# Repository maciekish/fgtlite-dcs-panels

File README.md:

# Another Warthog Project

This project has moved to https://github.com/maciekish/warthogathome

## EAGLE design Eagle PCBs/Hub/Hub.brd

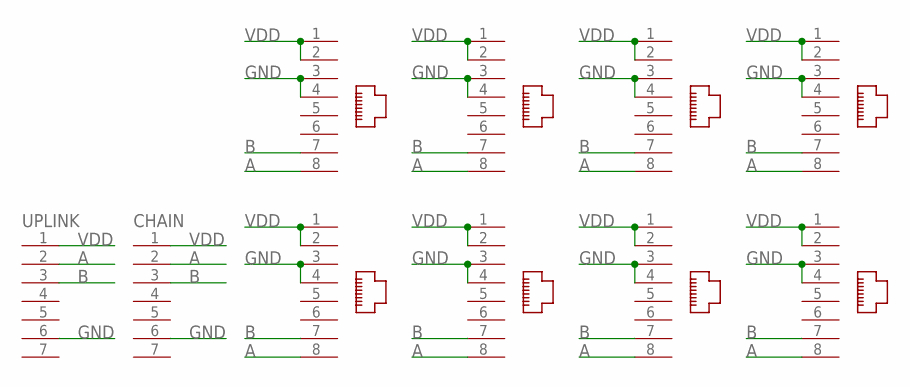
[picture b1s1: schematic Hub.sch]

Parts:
1, 2, 3, 4, 5, 6, 7, 8: RJ45-8P8C
CHAIN: GX12-7P
UPLINK: GX12-7P

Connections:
A: 1.8, 2.8, 3.8, 4.8, 5.8, 6.8, 7.8, 8.8, CHAIN.2, UPLINK.2
B: 1.7, 2.7, 3.7, 4.7, 5.7, 6.7, 7.7, 8.7, CHAIN.3, UPLINK.3
GND: 1.3, 1.4, 2.3, 2.4, 3.3, 3.4, 4.3, 4.4, 5.3, 5.4, 6.3, 6.4, 7.3, 7.4, 8.3, 8.4, CHAIN.6, UPLINK.6
VDD: 1.1, 1.2, 2.1, 2.2, 3.1, 3.2, 4.1, 4.2, 5.1, 5.2, 6.1, 6.2, 7.1, 7.2, 8.1, 8.2, CHAIN.1, UPLINK.1

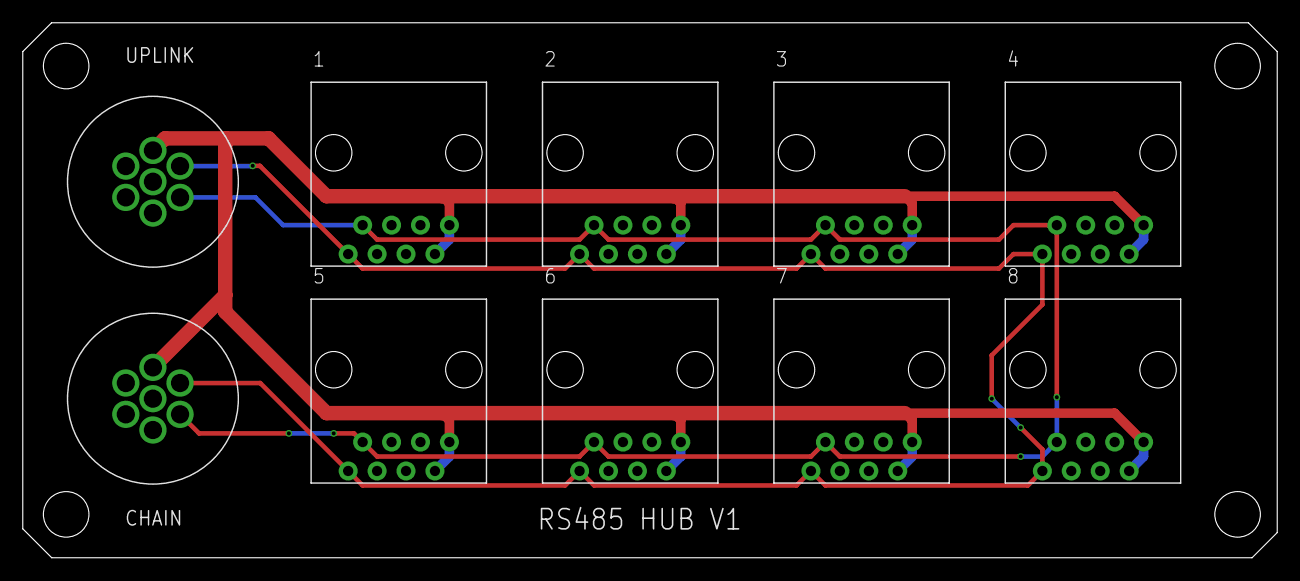
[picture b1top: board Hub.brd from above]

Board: 2 copper layers, 110.2 x 47.0 mm, 10 parts (0 on the bottom side), 4 nets.

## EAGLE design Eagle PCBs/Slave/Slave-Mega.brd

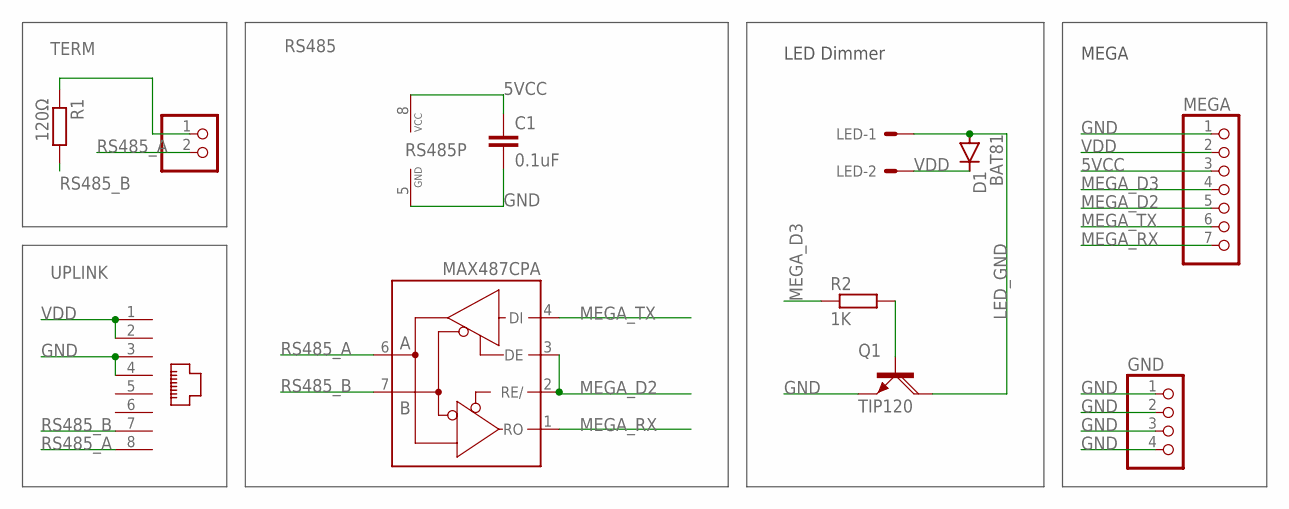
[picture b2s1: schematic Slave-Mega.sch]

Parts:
C1: 0.1uF; C025-025X050
D1: BAT81; DO34-7
GND: PINHD-1X4; 1X04
LED: KK-156-2
MEGA: PINHD-1X7; 1X07
Q1: TIP120; TO220AH
R1: 120Ω; 0204/7
R2: 1K; 0204/7
RS485: MAX487CPA; DIL08
TERM: PINHD-1X2; 1X02
UPLINK: RJ45-8P8C

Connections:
5VCC: C1.1, MEGA.3, RS485.8 (VCC)
GND: C1.2, GND.1, GND.2, GND.3, GND.4, MEGA.1, Q1.E, RS485.5 (GND), UPLINK.3, UPLINK.4
LED_GND: D1.A, LED.1, Q1.C
LED_PWM: Q1.B, R2.2
MEGA_D2: MEGA.5, RS485.2 (RE/), RS485.3 (DE)
MEGA_D3: MEGA.4, R2.1
MEGA_RX: MEGA.7, RS485.1 (RO)
MEGA_TX: MEGA.6, RS485.4 (DI)
RS485_A: RS485.6 (A), TERM.2, UPLINK.8
RS485_B: R1.2, RS485.7 (B), UPLINK.7
TERM: R1.1, TERM.1
VDD: D1.C, LED.2, MEGA.2, UPLINK.1, UPLINK.2

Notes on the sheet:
LED Dimmer
MEGA

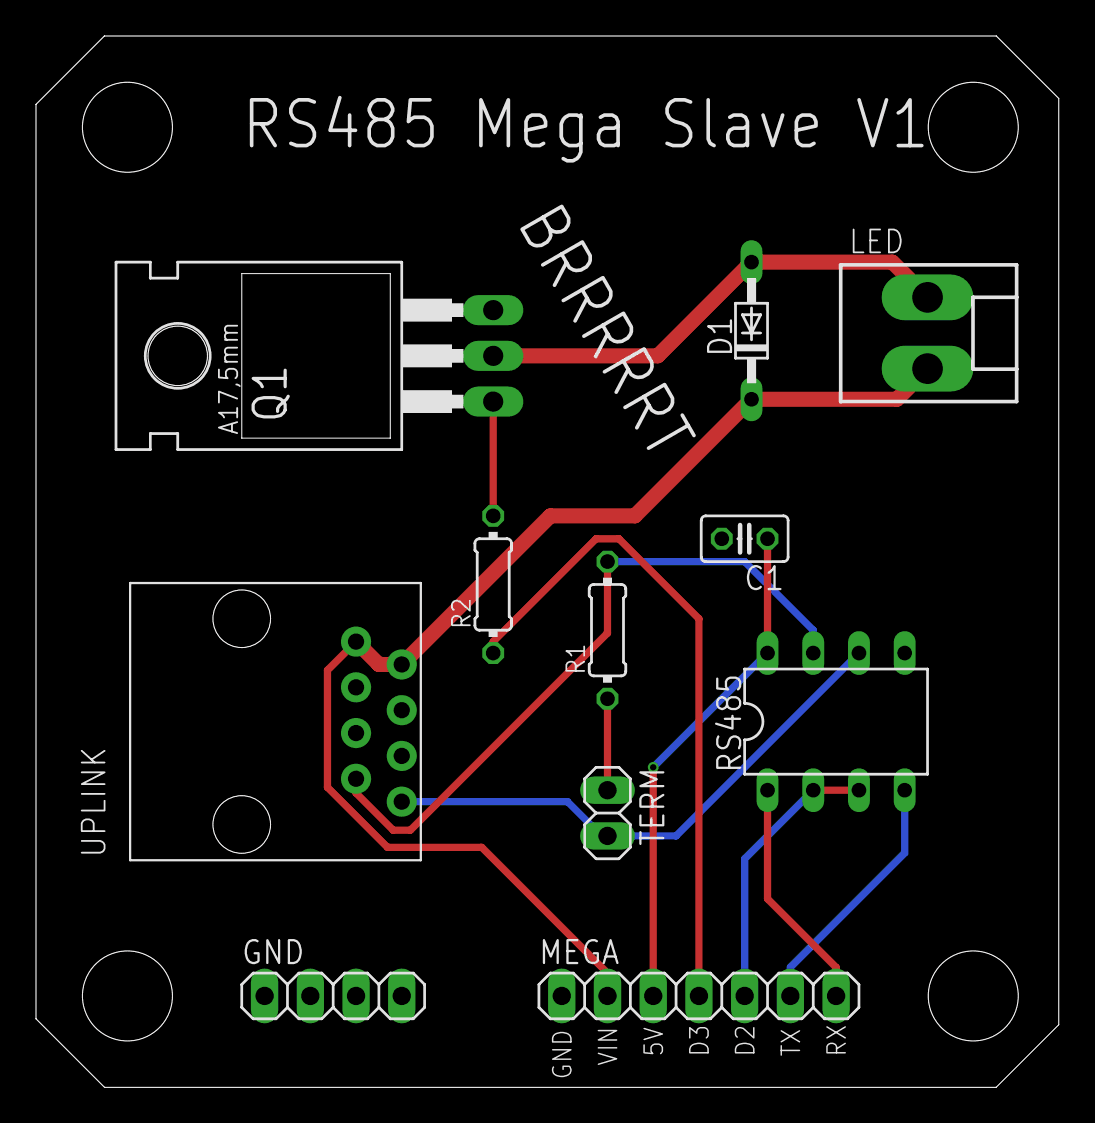
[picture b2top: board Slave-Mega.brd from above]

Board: 2 copper layers, 56.8 x 58.4 mm, 11 parts (0 on the bottom side), 12 nets.

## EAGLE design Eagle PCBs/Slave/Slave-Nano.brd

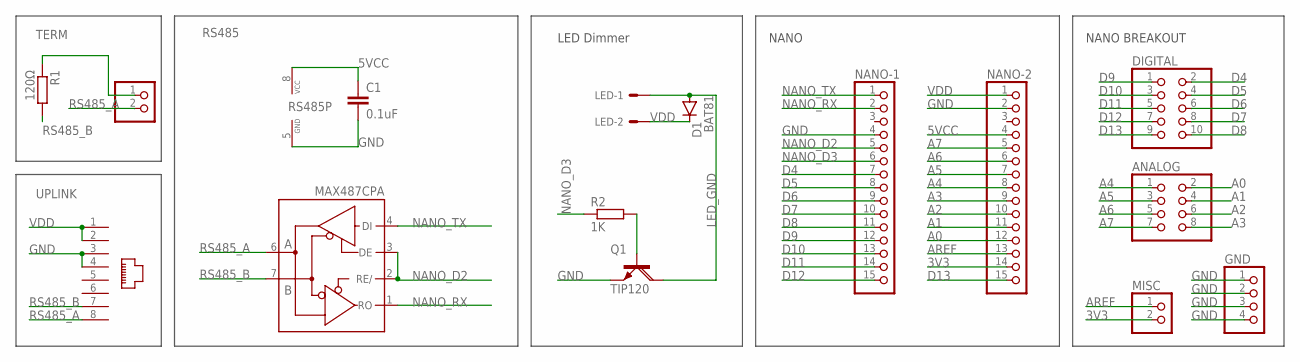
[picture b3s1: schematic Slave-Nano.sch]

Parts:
ANALOG: PINHD-2X4; 2X04
C1: 0.1uF; C025-025X050
D1: BAT81; DO34-7
DIGITAL: PINHD-2X5; 2X05
GND: PINHD-1X4; 1X04
LED: KK-156-2
MISC: PINHD-1X2; 1X02
NANO-1, NANO-2: PINHD-1X15; 1X15
Q1: TIP120; TO220AH
R1: 120Ω; 0204/7
R2: 1K; 0204/7
RS485: MAX487CPA; DIL08
TERM: PINHD-1X2; 1X02
UPLINK: RJ45-8P8C

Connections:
3V3: MISC.2, NANO-2.14
5VCC: C1.1, NANO-2.4, RS485.8 (VCC)
A0: ANALOG.2, NANO-2.12
A1: ANALOG.4, NANO-2.11
A2: ANALOG.6, NANO-2.10
A3: ANALOG.8, NANO-2.9
A4: ANALOG.1, NANO-2.8
A5: ANALOG.3, NANO-2.7
A6: ANALOG.5, NANO-2.6
A7: ANALOG.7, NANO-2.5
AREF: MISC.1, NANO-2.13
D4: DIGITAL.2, NANO-1.7
D5: DIGITAL.4, NANO-1.8
D6: DIGITAL.6, NANO-1.9
D7: DIGITAL.8, NANO-1.10
D8: DIGITAL.10, NANO-1.11
D9: DIGITAL.1, NANO-1.12
D10: DIGITAL.3, NANO-1.13
D11: DIGITAL.5, NANO-1.14
D12: DIGITAL.7, NANO-1.15
D13: DIGITAL.9, NANO-2.15
GND: C1.2, GND.1, GND.2, GND.3, GND.4, NANO-1.4, NANO-2.2, Q1.E, RS485.5 (GND), UPLINK.3, UPLINK.4
LED_GND: D1.A, LED.1, Q1.C
LED_PWM: Q1.B, R2.2
NANO_D2: NANO-1.5, RS485.2 (RE/), RS485.3 (DE)
NANO_D3: NANO-1.6, R2.1
NANO_RX: NANO-1.2, RS485.1 (RO)
NANO_TX: NANO-1.1, RS485.4 (DI)
RS485_A: RS485.6 (A), TERM.2, UPLINK.8
RS485_B: R1.2, RS485.7 (B), UPLINK.7
TERM: R1.1, TERM.1
VDD: D1.C, LED.2, NANO-2.1, UPLINK.1, UPLINK.2

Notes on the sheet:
LED Dimmer
NANO
NANO BREAKOUT

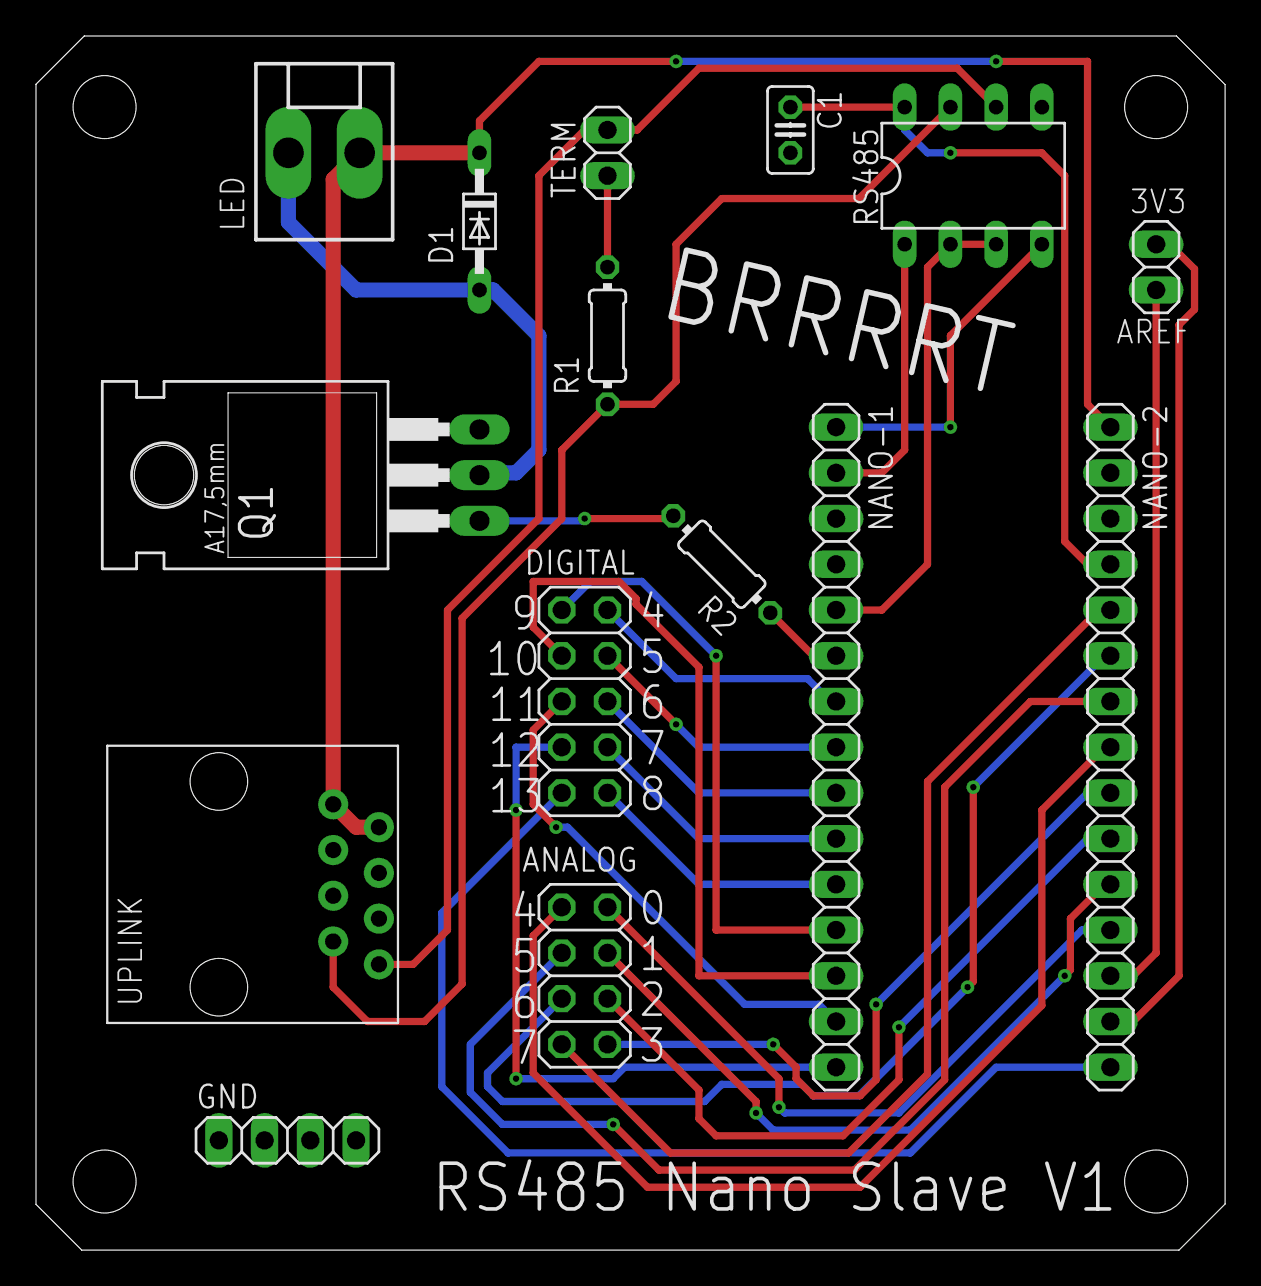
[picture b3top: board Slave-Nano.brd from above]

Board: 2 copper layers, 66.1 x 67.5 mm, 15 parts (0 on the bottom side), 32 nets.

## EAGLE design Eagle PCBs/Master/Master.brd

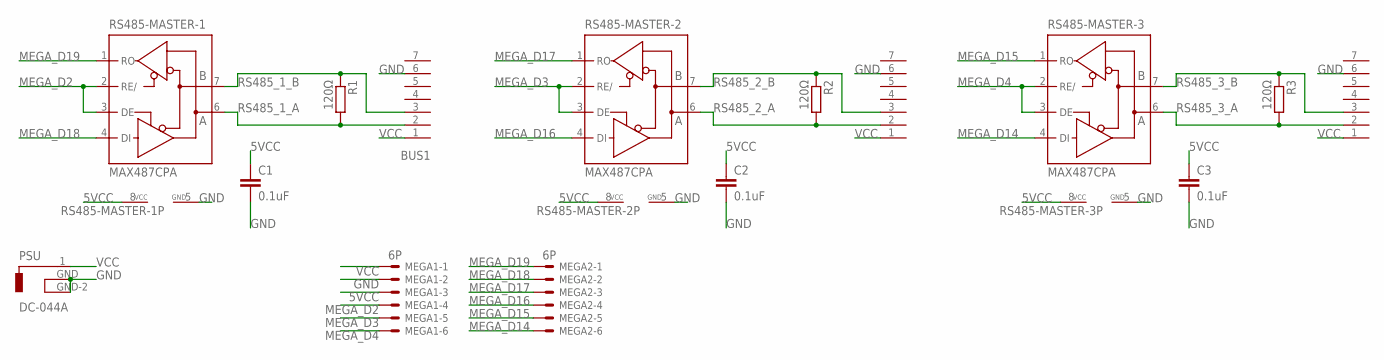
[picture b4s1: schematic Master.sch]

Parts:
BUS1, BUS2, BUS3: GX12-7P
C1, C2, C3: 0.1uF; C025-025X050
MEGA1, MEGA2: 6P; 22-23-2061
PSU: DC-044A
R1, R2, R3: 120Ω; 0207/10
RS485-MASTER-1, RS485-MASTER-2, RS485-MASTER-3: MAX487CPA; DIL08

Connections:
5VCC: C1.1, C2.1, C3.1, MEGA1.3, RS485-MASTER-1.8 (VCC), RS485-MASTER-2.8 (VCC), RS485-MASTER-3.8 (VCC)
GND: BUS1.6, BUS2.6, BUS3.6, C1.2, C2.2, C3.2, MEGA1.2, PSU.GND, PSU.GND-2, RS485-MASTER-1.5 (GND), RS485-MASTER-2.5 (GND), RS485-MASTER-3.5 (GND)
MEGA_D2: MEGA1.4, RS485-MASTER-1.2 (RE/), RS485-MASTER-1.3 (DE)
MEGA_D3: MEGA1.5, RS485-MASTER-2.2 (RE/), RS485-MASTER-2.3 (DE)
MEGA_D4: MEGA1.6, RS485-MASTER-3.2 (RE/), RS485-MASTER-3.3 (DE)
MEGA_D14: MEGA2.6, RS485-MASTER-3.4 (DI)
MEGA_D15: MEGA2.5, RS485-MASTER-3.1 (RO)
MEGA_D16: MEGA2.4, RS485-MASTER-2.4 (DI)
MEGA_D17: MEGA2.3, RS485-MASTER-2.1 (RO)
MEGA_D18: MEGA2.2, RS485-MASTER-1.4 (DI)
MEGA_D19: MEGA2.1, RS485-MASTER-1.1 (RO)
RS485_1_A: BUS1.2, R1.2, RS485-MASTER-1.6 (A)
RS485_1_B: BUS1.3, R1.1, RS485-MASTER-1.7 (B)
RS485_2_A: BUS2.2, R2.2, RS485-MASTER-2.6 (A)
RS485_2_B: BUS2.3, R2.1, RS485-MASTER-2.7 (B)
RS485_3_A: BUS3.2, R3.2, RS485-MASTER-3.6 (A)
RS485_3_B: BUS3.3, R3.1, RS485-MASTER-3.7 (B)
VCC: BUS1.1, BUS2.1, BUS3.1, MEGA1.1, PSU.1

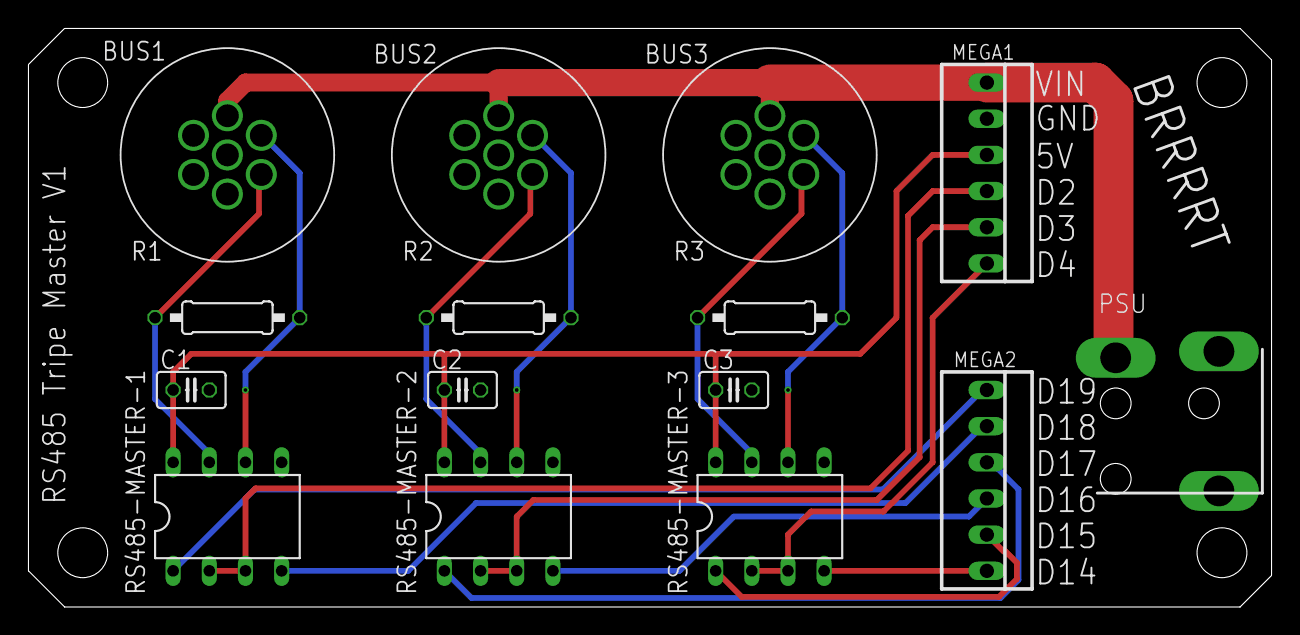
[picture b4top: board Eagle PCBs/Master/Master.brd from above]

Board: 2 copper layers, 87.3 x 40.6 mm, 15 parts (0 on the bottom side), 18 nets.

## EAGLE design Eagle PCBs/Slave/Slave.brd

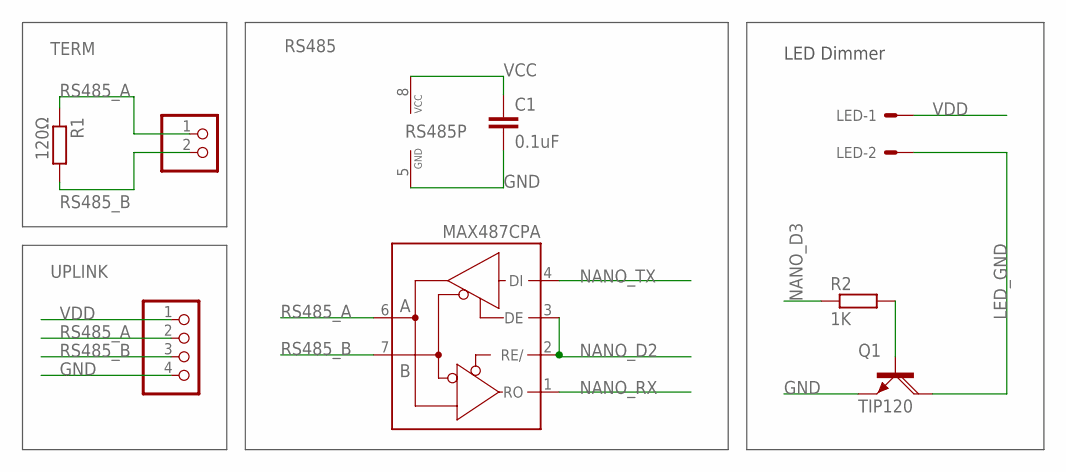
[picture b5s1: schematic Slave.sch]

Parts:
C1: 0.1uF; C025-025X050
LED: KK-156-2
Q1: TIP120; TO220AH
R1: 120Ω; 0207/10
R2: 1K; 0207/10
RS485: MAX487CPA; DIL08
TERM: PINHD-1X2; 1X02
UPLINK: PINHD-1X4; 1X04

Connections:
GND: C1.2, Q1.E, RS485.5 (GND), UPLINK.4
LED_GND: LED.2, Q1.C
unnamed: Q1.B, R2.2
NANO_D2: RS485.2 (RE/), RS485.3 (DE)
NANO_D3: R2.1
NANO_RX: RS485.1 (RO)
NANO_TX: RS485.4 (DI)
RS485_A: R1.1, RS485.6 (A), TERM.1, UPLINK.2
RS485_B: R1.2, RS485.7 (B), TERM.2, UPLINK.3
VCC: C1.1, RS485.8 (VCC)
VDD: LED.1, UPLINK.1

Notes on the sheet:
LED Dimmer

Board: 2 copper layers, 8 parts (0 on the bottom side), 8 nets, no tracks yet.

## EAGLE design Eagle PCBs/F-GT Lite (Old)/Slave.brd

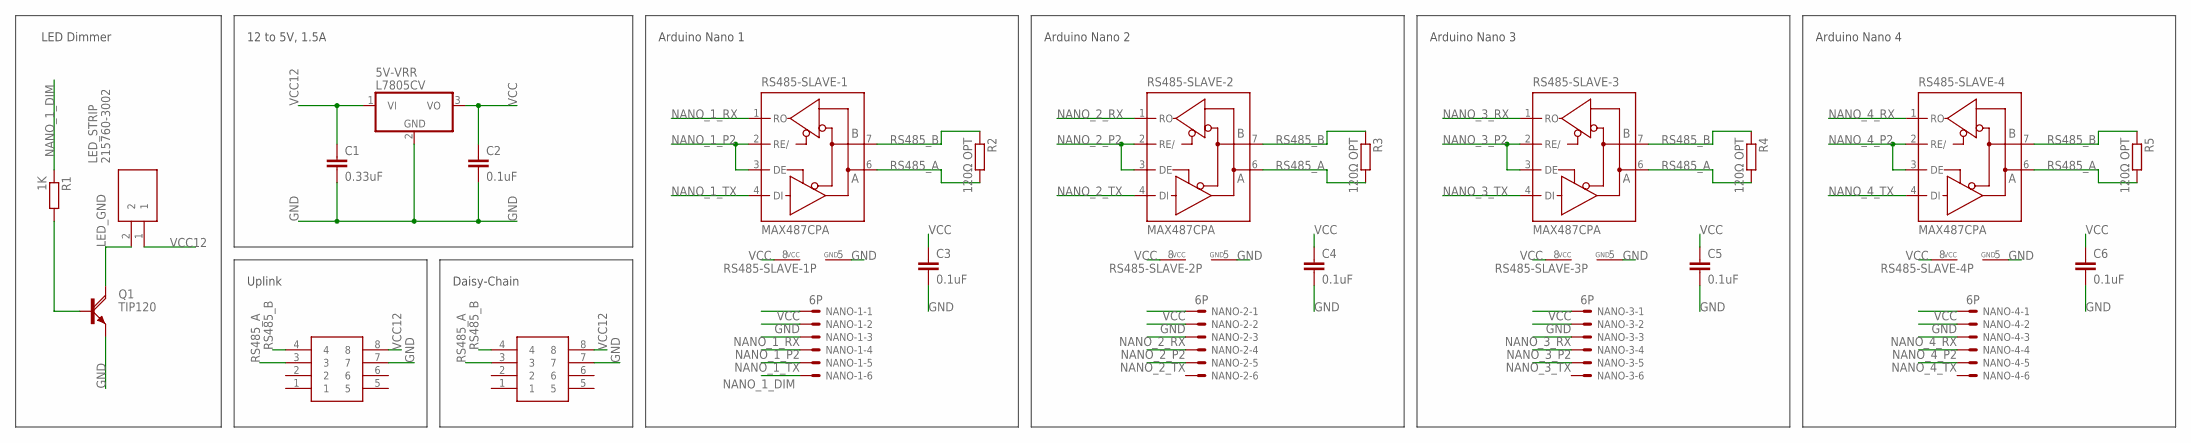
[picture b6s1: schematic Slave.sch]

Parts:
5V-VRR: L7805CV; TO220H
C1: 0.33uF; C025-025X050
C2, C3, C4, C5, C6: 0.1uF; C025-025X050
LED_STRIP: 215760-3002; 215760-YY02
NANO-1, NANO-2, NANO-3, NANO-4: 6P; 22-23-2061
Q1: TIP120; TO220AH
R1: 1K; 0207/10
R2, R3, R4, R5: 120Ω OPT; 0207/10
RS485-SLAVE-1, RS485-SLAVE-2, RS485-SLAVE-3, RS485-SLAVE-4: MAX487CPA; DIL08
UPLINK, UPLINK1: 212528-0801; 212528-08YY

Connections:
GND: 5V-VRR.2 (GND), C1.2, C2.2, C3.2, C4.2, C5.2, C6.2, NANO-1.2, NANO-2.2, NANO-3.2, NANO-4.2, Q1.E, RS485-SLAVE-1.5 (GND), RS485-SLAVE-2.5 (GND), RS485-SLAVE-3.5 (GND), RS485-SLAVE-4.5 (GND), UPLINK.7, UPLINK1.7
LED_GND: LED_STRIP.2, Q1.C
unnamed: Q1.B, R1.2
NANO_1_DIM: NANO-1.6, R1.1
NANO_1_P2: NANO-1.4, RS485-SLAVE-1.2 (RE/), RS485-SLAVE-1.3 (DE)
NANO_1_RX: NANO-1.3, RS485-SLAVE-1.1 (RO)
NANO_1_TX: NANO-1.5, RS485-SLAVE-1.4 (DI)
NANO_2_P2: NANO-2.4, RS485-SLAVE-2.2 (RE/), RS485-SLAVE-2.3 (DE)
NANO_2_RX: NANO-2.3, RS485-SLAVE-2.1 (RO)
NANO_2_TX: NANO-2.5, RS485-SLAVE-2.4 (DI)
NANO_3_P2: NANO-3.4, RS485-SLAVE-3.2 (RE/), RS485-SLAVE-3.3 (DE)
NANO_3_RX: NANO-3.3, RS485-SLAVE-3.1 (RO)
NANO_3_TX: NANO-3.5, RS485-SLAVE-3.4 (DI)
NANO_4_P2: NANO-4.4, RS485-SLAVE-4.2 (RE/), RS485-SLAVE-4.3 (DE)
NANO_4_RX: NANO-4.3, RS485-SLAVE-4.1 (RO)
NANO_4_TX: NANO-4.5, RS485-SLAVE-4.4 (DI)
RS485_A: R2.2, R3.2, R4.2, R5.2, RS485-SLAVE-1.6 (A), RS485-SLAVE-2.6 (A), RS485-SLAVE-3.6 (A), RS485-SLAVE-4.6 (A), UPLINK.3, UPLINK1.3
RS485_B: R2.1, R3.1, R4.1, R5.1, RS485-SLAVE-1.7 (B), RS485-SLAVE-2.7 (B), RS485-SLAVE-3.7 (B), RS485-SLAVE-4.7 (B), UPLINK.4, UPLINK1.4
VCC: 5V-VRR.3 (VO), C2.1, C3.1, C4.1, C5.1, C6.1, NANO-1.1, NANO-2.1, NANO-3.1, NANO-4.1, RS485-SLAVE-1.8 (VCC), RS485-SLAVE-2.8 (VCC), RS485-SLAVE-3.8 (VCC), RS485-SLAVE-4.8 (VCC)
VCC12: 5V-VRR.1 (VI), C1.1, LED_STRIP.1, UPLINK.8, UPLINK1.8

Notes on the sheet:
LED Dimmer
12 to 5V, 1.5A
Arduino Nano 1
Uplink
Daisy-Chain
Arduino Nano 2
Arduino Nano 3
Arduino Nano 4

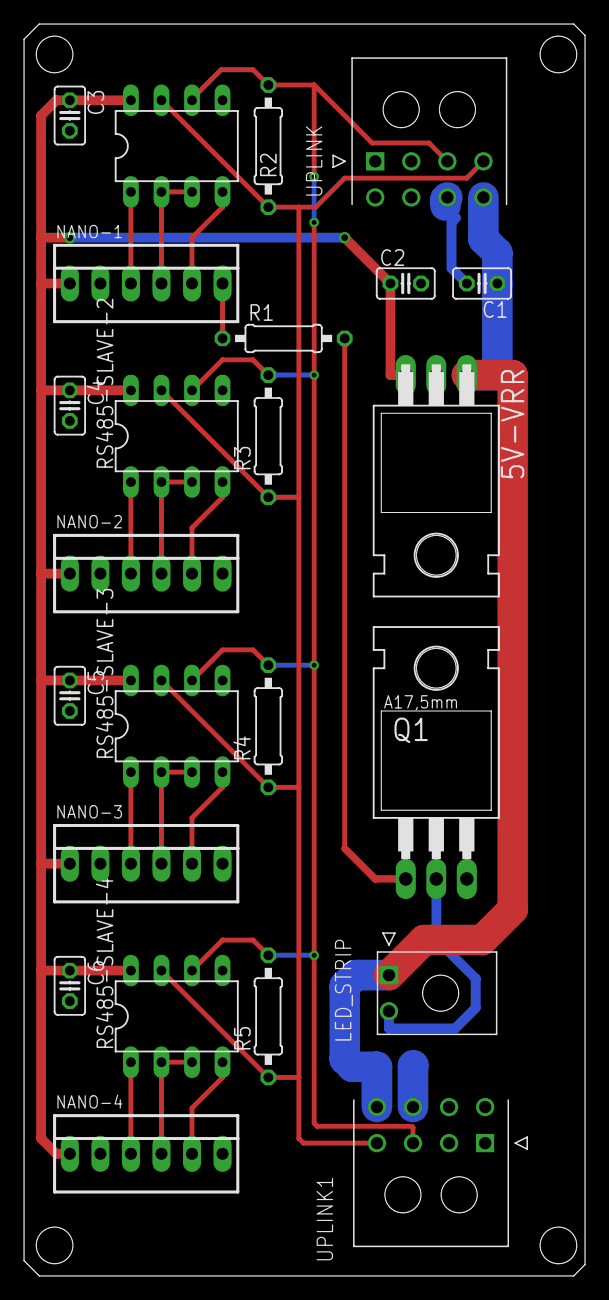
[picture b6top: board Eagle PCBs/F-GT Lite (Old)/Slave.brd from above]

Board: 2 copper layers, 46.7 x 104.1 mm, 24 parts (0 on the bottom side), 20 nets.

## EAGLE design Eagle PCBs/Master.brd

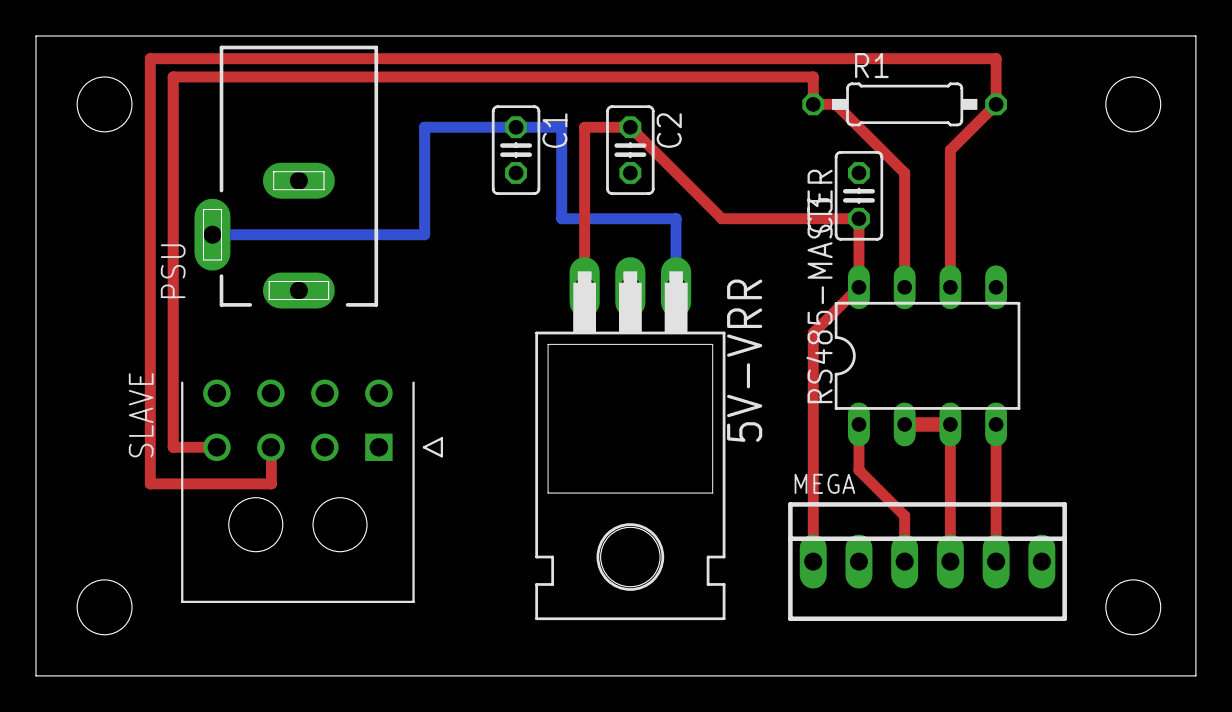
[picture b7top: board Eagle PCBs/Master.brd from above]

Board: 2 copper layers, 64.4 x 35.5 mm, 9 parts (0 on the bottom side), 8 nets.

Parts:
5V-VRR: L7805CV; TO220H
C1: 0.33uF; C025-025X050
C2, C3: 0.1uF; C025-025X050
MEGA: 22-23-2061
PSU: 12VDC C+; DCJ0202
R1: 120Ω; 0207/10
RS485-MASTER: MAX487CPA; DIL08
SLAVE: 212528-0801; 212528-08YY

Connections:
GND: 5V-VRR.2, C1.2, C2.2, C3.2, MEGA.2, PSU.1, RS485-MASTER.5, SLAVE.7
MEGA_P2: MEGA.4, RS485-MASTER.2, RS485-MASTER.3
MEGA_P18: MEGA.5, RS485-MASTER.4
MEGA_P19: MEGA.3, RS485-MASTER.1
RS485_A: R1.2, RS485-MASTER.6, SLAVE.3
RS485_B: R1.1, RS485-MASTER.7, SLAVE.4
VCC: 5V-VRR.1, C1.1, PSU.2, SLAVE.8
VDD: 5V-VRR.3, C2.1, C3.1, MEGA.1, RS485-MASTER.8

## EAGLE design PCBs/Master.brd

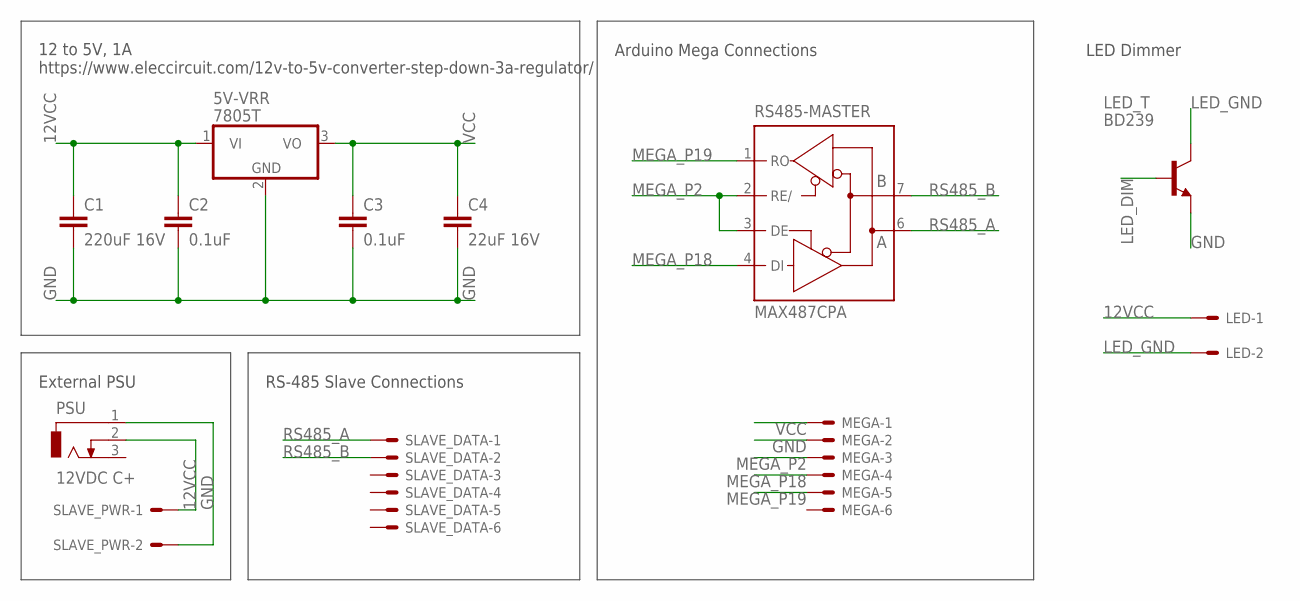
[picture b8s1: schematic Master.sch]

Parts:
5V-VRR: 7805T; TO220H
C1: 220uF 16V; C025-025X050
C2, C3: 0.1uF; C025-025X050
C4: 22uF 16V; C025-025X050
LED: KK-156-2
LED_T: BD239; TO220
MEGA: 22-23-2061
PSU: 12VDC C+; DCJ0202
RS485-MASTER: MAX487CPA; DIL08
SLAVE_DATA: 22-23-2061
SLAVE_PWR: KK-156-2

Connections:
12VCC: 5V-VRR.1 (VI), C1.1, C2.1, LED.1, PSU.2, SLAVE_PWR.1
GND: 5V-VRR.2 (GND), C1.2, C2.2, C3.2, C4.2, LED_T.3 (E), MEGA.2, PSU.1, RS485-MASTER.5 (GND), SLAVE_PWR.2
LED_DIM: LED_T.1 (B)
LED_GND: LED.2, LED_T.2 (C)
MEGA_P2: MEGA.3, RS485-MASTER.2 (RE/), RS485-MASTER.3 (DE)
MEGA_P18: MEGA.4, RS485-MASTER.4 (DI)
MEGA_P19: MEGA.5, RS485-MASTER.1 (RO)
RS485_A: RS485-MASTER.6 (A), SLAVE_DATA.1
RS485_B: RS485-MASTER.7 (B), SLAVE_DATA.2
VCC: 5V-VRR.3 (VO), C3.1, C4.1, MEGA.1, RS485-MASTER.8 (VCC)

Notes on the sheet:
12 to 5V, 1A https://www.eleccircuit.com/12v-to-5v-converter-step-down-3a-regulator/
External PSU
Arduino Mega Connections
RS-485 Slave Connections
LED Dimmer

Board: 2 copper layers, 12 parts (0 on the bottom side), 9 nets, no tracks yet.

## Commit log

2022-07-14 Folder structure
2022-07-14 Folder structure and libraries
2022-07-15 Master PCB WIP
2022-07-17 Slave PCB WIP
2022-07-18 Updated DC Barrel Jack
    DC-044A
2022-07-26 Changed TIP120 resistor value and added some WIP files
2022-07-28 Added reference panel designs from The Warthog Project and a README with attribution.
2022-07-29 Created new Master PCB Added Panel Designs from The Warthog Project General Cleanup
2022-07-29 PCB WIP
2022-07-29 Added LED circuit to Slave PCB
2022-08-01 Updated GX12 footprint and finalized first revison of Master PCB
2022-08-01 New slave PCB
2022-08-01 Cleaned up Eagle backup-files
2022-08-01 Removed duplicate
2022-08-01 New mega slave PCB Increased clearances on master PCB
2022-08-01 Fixed D4 silkscreen on master PCB
2022-08-01 Fixed silkscreen
2022-08-01 Added Hub PCB
